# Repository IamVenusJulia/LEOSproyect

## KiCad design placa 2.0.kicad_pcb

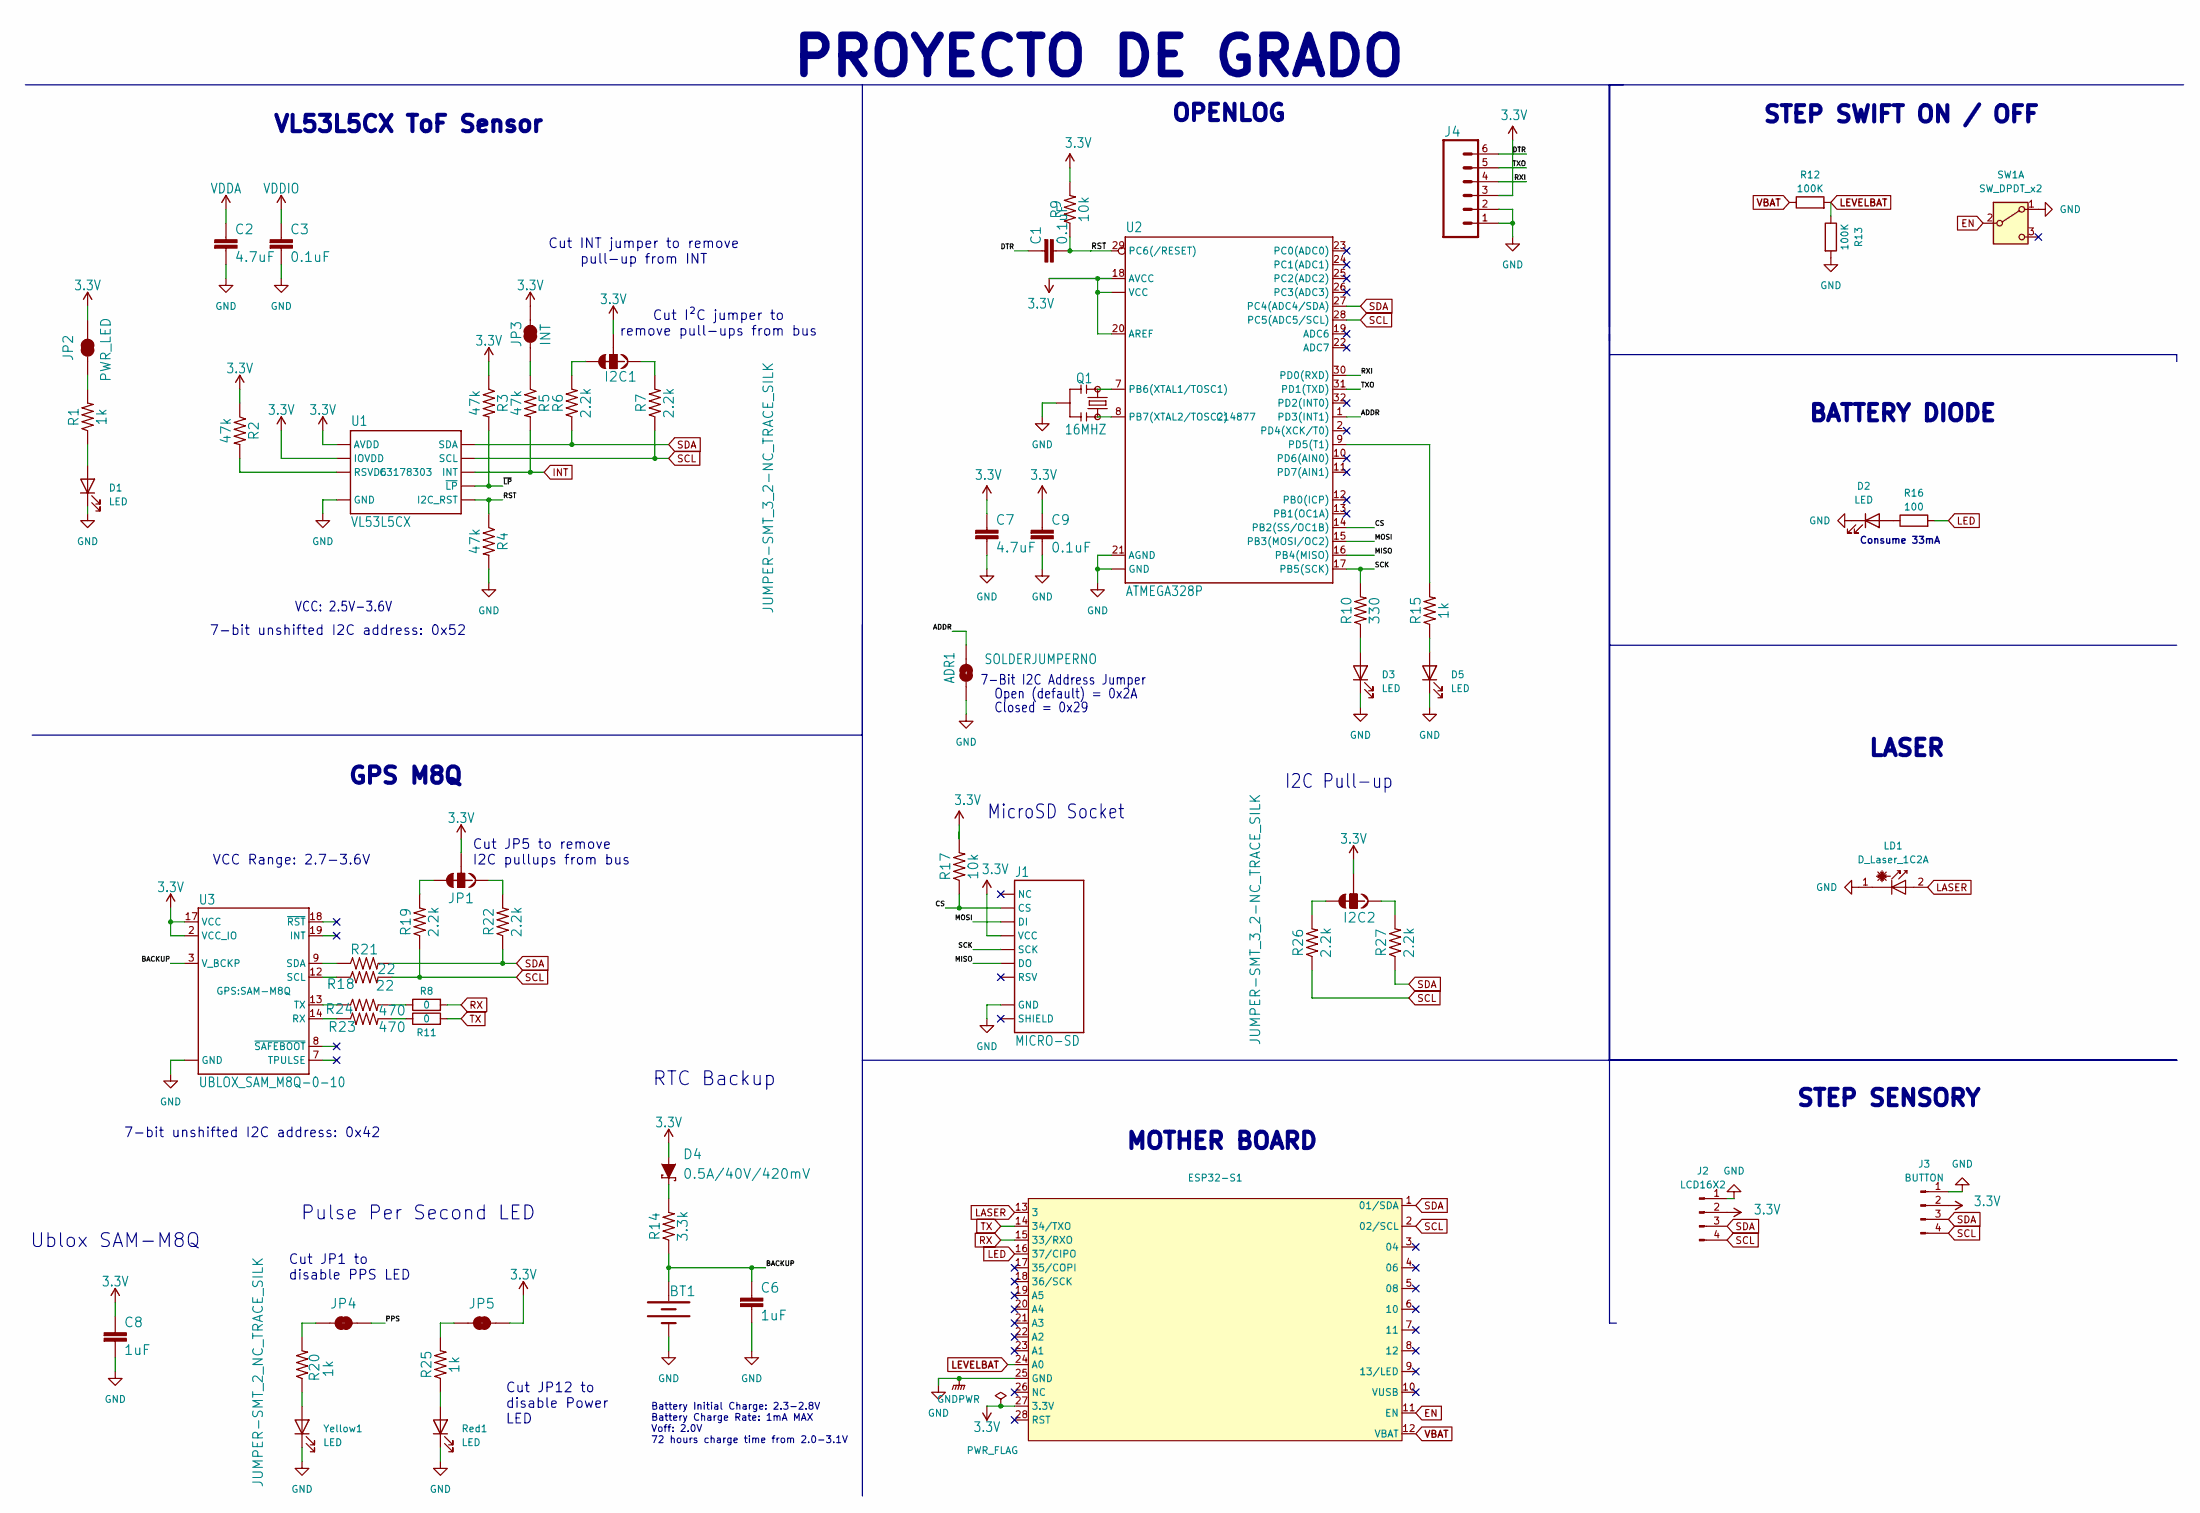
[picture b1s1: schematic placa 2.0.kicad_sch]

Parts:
ADR1: SOLDERJUMPERNO; SJ_2S-NO
BT1: 6.8MM_COIN_CELL; ML414H_IV01E
C1, C3, C9: 0.1uF; C_0603_1608Metric
C2, C7: 4.7uF; C_0603_1608Metric
C6, C8: 1uF; C_0603_1608Metric
D1, D3, D5: LED; LED_1206_3216Metric
D2: LED; LED_D3.0mm_Horizontal_O6.35mm_Z10.0mm
D4: 0.5A/40V/420mV; D_SOD-323
ESP32-S1: ESP32-S2
I2C1, I2C2: JUMPER-SMT_3_2-NC_TRACE_SILK; SMT-JUMPER_3_2-NC_TRACE_SILK
J1: MICRO-SD; MICRO-SD-SOCKET
J2: LCD16X2; JST_PH_B4B-PH-K_1x04_P2.00mm_Vertical
J3: BUTTON; JST_PH_B4B-PH-K_1x04_P2.00mm_Vertical
J4: CONN_06NO_SILK_NO_POP; PinHeader_1x06_P2.54mm_Vertical
JP1: JUMPER-SMT_3_2-NC_TRACE_SILK; SMT-JUMPER_3_2-NC_TRACE_SILK
JP2: PWR_LED; SMT-JUMPER_2_NC_TRACE_SILK
JP3: INT; SMT-JUMPER_2_NC_TRACE_SILK
JP4, JP5: JUMPER-SMT_2_NC_TRACE_SILK; SMT-JUMPER_2_NC_TRACE_SILK
LD1: D_Laser_1C2A; LaserDiode_TO18-D5.6-3
Q1: 16MHZ; RESONATOR-SMD
R1, R15, R20, R25: 1k; R_0603_1608Metric
R2, R3, R4, R5: 47k; R_0603_1608Metric
R6, R7, R19, R22, R26, R27: 2.2k; R_0603_1608Metric
R8, R11: 0; 1206
R9, R17: 10k; R_0603_1608Metric
R10: 330; R_0603_1608Metric
R12, R13: 100K; 1206
R14: 3.3k; R_0603_1608Metric
R16: 100; 1206
R18, R21: 22; R_0603_1608Metric
R23, R24: 470; R_0603_1608Metric
Red1: LED; LED_1206_3216Metric
SW1: SW_DPDT_x2; Molex_KK-254_AE-6410-02A_1x02_P2.54mm_Vertical
U1: VL53L5CX; LCSC C3178303
U2: ATMEGA328P; TQFP-32_7x7mm; LCSC C14877
U3: UBLOX_SAM_M8Q-0-10; SAM-M8Q
Yellow1: LED; LED_1206_3216Metric

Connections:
3.3V: C7.1, C8.1, C9.1, D4.2 (A), ESP32-S1.27 (3.3V), I2C1.2, I2C2.2, J1.VCC, J2.2, J3.2, J4.3, JP1.2, JP2.2, JP3.2, JP5.2, R2.1, R3.1, R9.2, R17.2, U1.A4 (IOVDD), U1.B1 (AVDD), U1.B7 (AVDD), U2.4 (VCC), U2.6 (VCC), U2.18 (AVCC), U2.20 (AREF), U3.2 (VCC_IO), U3.17 (VCC)
/ADDR: ADR1.2, U2.1 (PD3(INT1))
/BACKUP: BT1.+, C6.1, R14.1, U3.3 (V_BCKP)
/CS: J1.CS, R17.1, U2.14 (PB2(SS/OC1B))
/DTR: C1.2, J4.6
/MISO: J1.DO, U2.16 (PB4(MISO))
/MOSI: J1.DI, U2.15 (PB3(MOSI/OC2))
/PPS: JP4.2
/RST: C1.1, R4.1, R9.1, U1.A1 (I2C_RST), U2.29 (PC6(/RESET))
/RXI: J4.4, U2.30 (PD0(RXD))
/SCK: J1.SCLK (SCK), R10.2, U2.17 (PB5(SCK))
/TXO: J4.5, U2.31 (PD1(TXD))
/~LP: R3.2, U1.A5 (~LP)
EN: ESP32-S1.11 (EN), SW1.2 (B)
GND: ADR1.1, BT1.-, C2.2, C3.2, C6.2, C7.2, C8.2, C9.2, D1.1 (K), D2.1 (K), D3.1 (K), D5.1 (K), ESP32-S1.25 (GND), J1.GND, J2.1, J3.1, J4.1, J4.2, LD1.1 (K), Q1.2, R4.2, R13.2, Red1.1 (K), SW1.1 (A), U1.A2 (GND), U1.A6 (GND), U1.A7 (GND), U1.B4 (GND), U1.C1 (GND), U1.C6 (GND), U1.C7 (GND), U2.3 (GND), U2.5 (GND), U2.21 (AGND), U3.1 (GND), U3.4 (GND), U3.5 (GND), U3.6 (GND), U3.10 (GND), U3.11 (GND), U3.15 (GND), U3.16 (GND), U3.20 (GND), Yellow1.1 (K)
INT: R5.2, U1.A3 (INT)
LASER: ESP32-S1.13 (3), LD1.2 (A)
LED: ESP32-S1.16 (37/CIPO), R16.2
LEVELBAT: ESP32-S1.24 (A0), R12.2, R13.1
unnamed: D1.2 (A), R1.1
unnamed: D2.2 (A), R16.1
unnamed: D3.2 (A), R10.1
unnamed: D4.1 (C), R14.2
unnamed: D5.2 (A), R15.1
unnamed: I2C1.1, R7.2
unnamed: I2C1.3, R6.2
unnamed: I2C2.1, R27.2
unnamed: I2C2.3, R26.2
unnamed: JP1.1, R22.2
unnamed: JP1.3, R19.2
unnamed: JP2.1, R1.2
unnamed: JP3.1, R5.1
unnamed: JP4.1, R20.2
unnamed: JP5.1, R25.2
unnamed: R11.1, R23.2
unnamed: R8.1, R24.2
unnamed: R25.1, Red1.2 (A)
unnamed: R2.2, U1.C2 (RSVD6)
unnamed: Q1.3, U2.7 (PB6(XTAL1/TOSC1))
unnamed: Q1.1, U2.8 (PB7(XTAL2/TOSC2))
unnamed: R15.2, U2.9 (PD5(T1))
unnamed: R23.1, U3.14 (RX)
unnamed: R18.1, U3.12 (SCL)
unnamed: R21.1, U3.9 (SDA)
unnamed: R24.1, U3.13 (TX)
unnamed: R20.1, Yellow1.2 (A)
RX: ESP32-S1.15 (33/RXO), R8.2
SCL: ESP32-S1.2 (02/SCL), J2.4, J3.4, R7.1, R18.2, R19.1, R26.1, U1.C4 (SCL), U2.28 (PC5(ADC5/SCL))
SDA: ESP32-S1.1 (01/SDA), J2.3, J3.3, R6.1, R21.2, R22.1, R27.1, U1.C3 (SDA), U2.27 (PC4(ADC4/SDA))
TX: ESP32-S1.14 (34/TXO), R11.2
VBAT: ESP32-S1.12 (VBAT), R12.1
VDDA: C2.1
VDDIO: C3.1

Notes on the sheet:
Cut JP12 to disable Power LED
Cut JP5 to remove I2C pullups from bus
VCC Range: 2.7-3.6V
Pulse Per Second LED
PROYECTO DE GRADO
BATTERY DIODE
Consume 33mA
Cut I²C jumper to remove pull-ups from bus
Cut INT jumper to remove pull-up from INT
RTC Backup
VCC: 2.5V-3.6V
GPS M8Q
7-Bit I2C Address Jumper
Cut JP1 to disable PPS LED
Ublox SAM-M8Q
7-bit unshifted I2C address: 0x52
STEP SWIFT ON / OFF
MOTHER BOARD
Closed = 0x29
STEP SENSORY
VL53L5CX ToF Sensor
I2C Pull-up
OPENLOG
LASER
Open (default) = 0x2A
MicroSD Socket
Battery Initial Charge: 2.3-2.8V Battery Charge Rate: 1mA MAX Voff: 2.0V 72 hours charge time from 2.0-3.1V
7-bit unshifted I2C address: 0x42

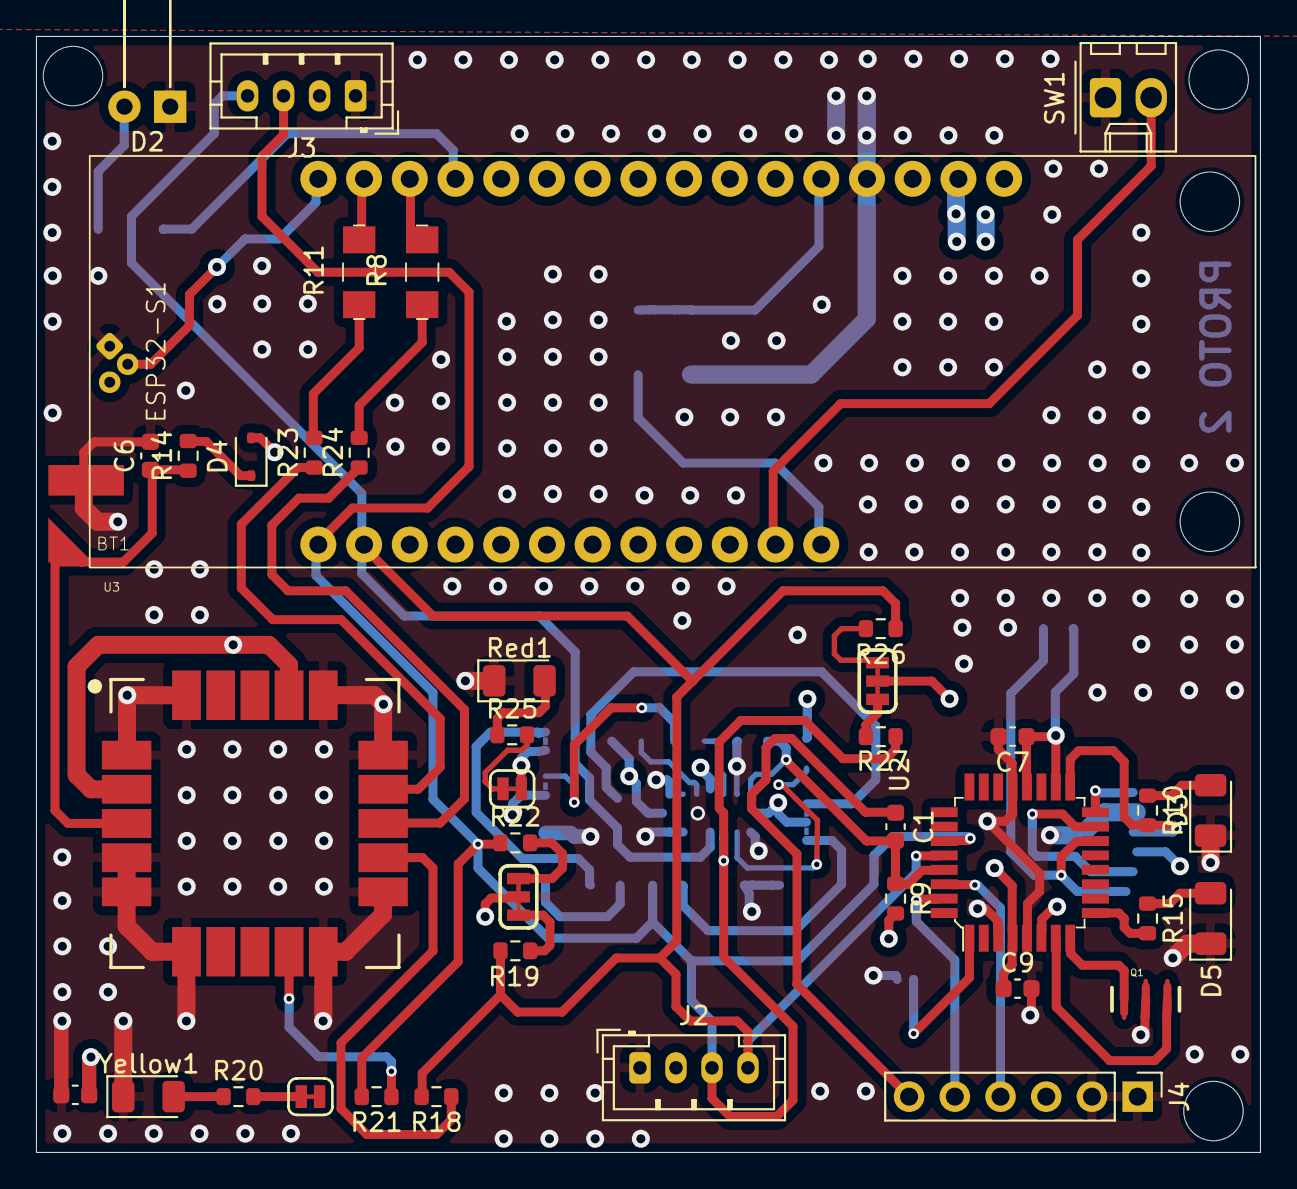
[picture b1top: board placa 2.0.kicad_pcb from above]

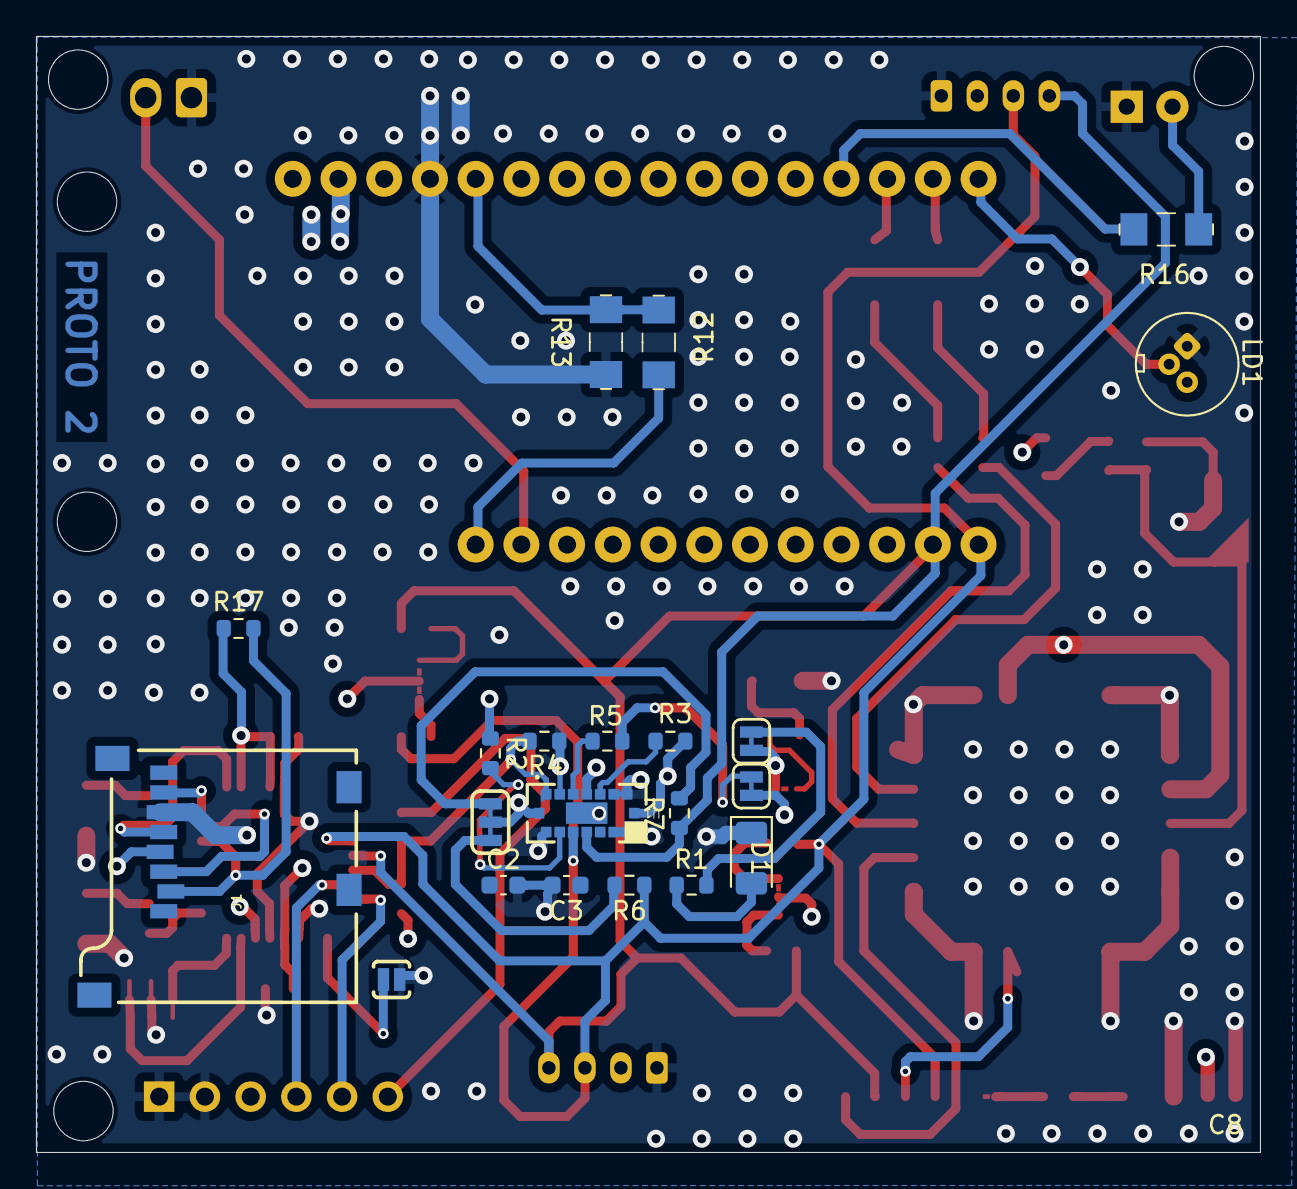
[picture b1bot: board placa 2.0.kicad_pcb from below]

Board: 4 copper layers, 68.0 x 62.0 mm, 61 parts (21 on the bottom side), 50 nets.

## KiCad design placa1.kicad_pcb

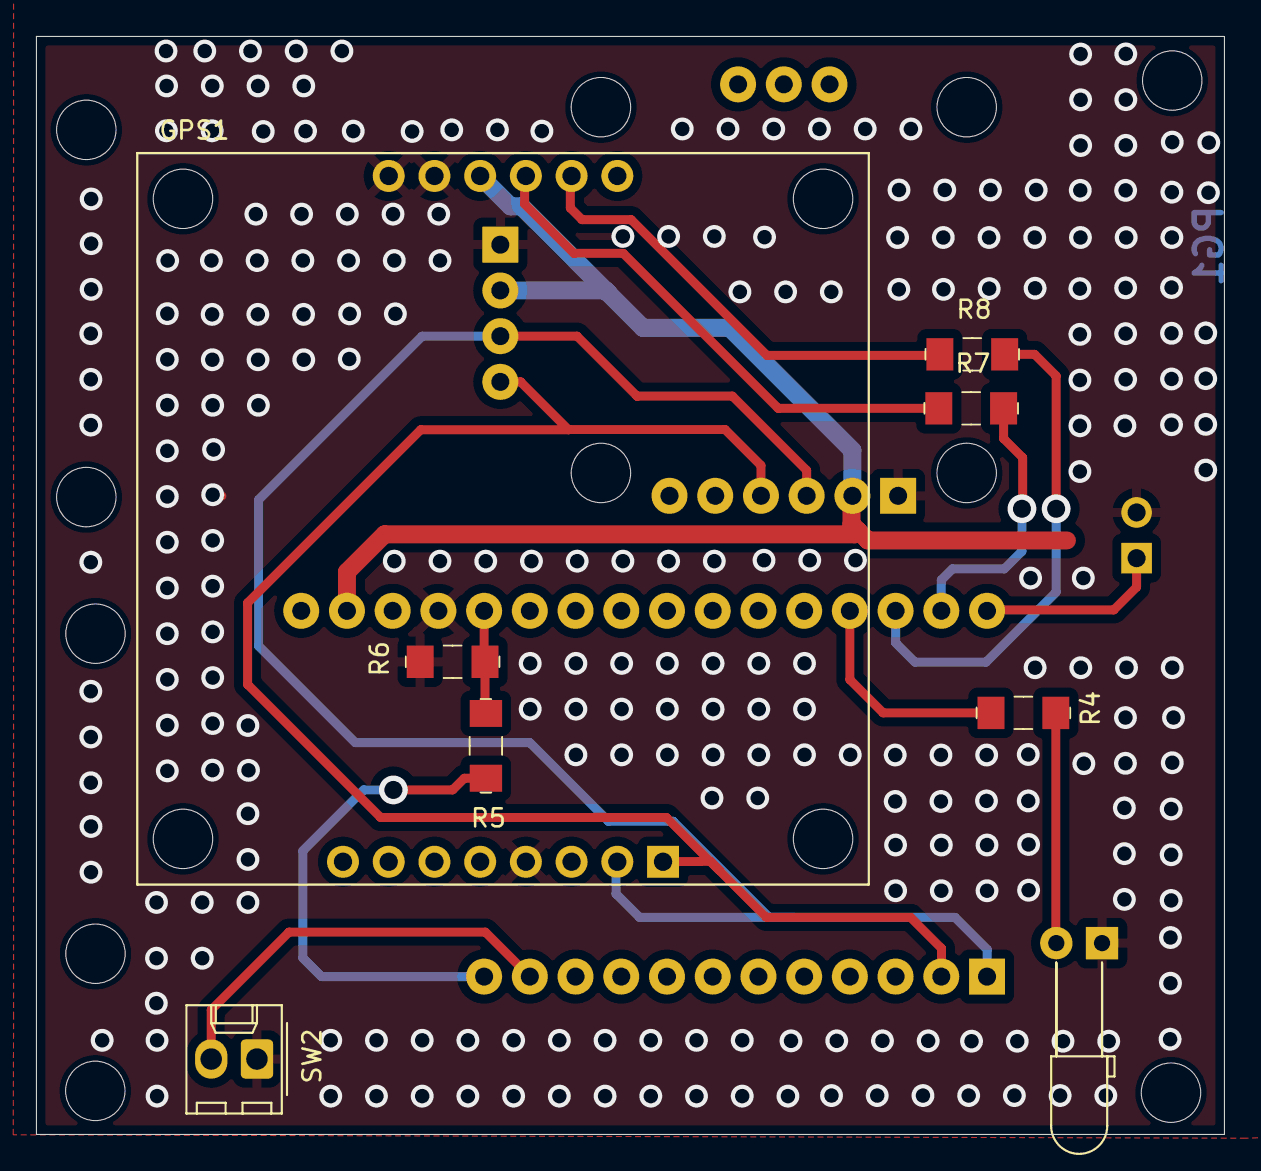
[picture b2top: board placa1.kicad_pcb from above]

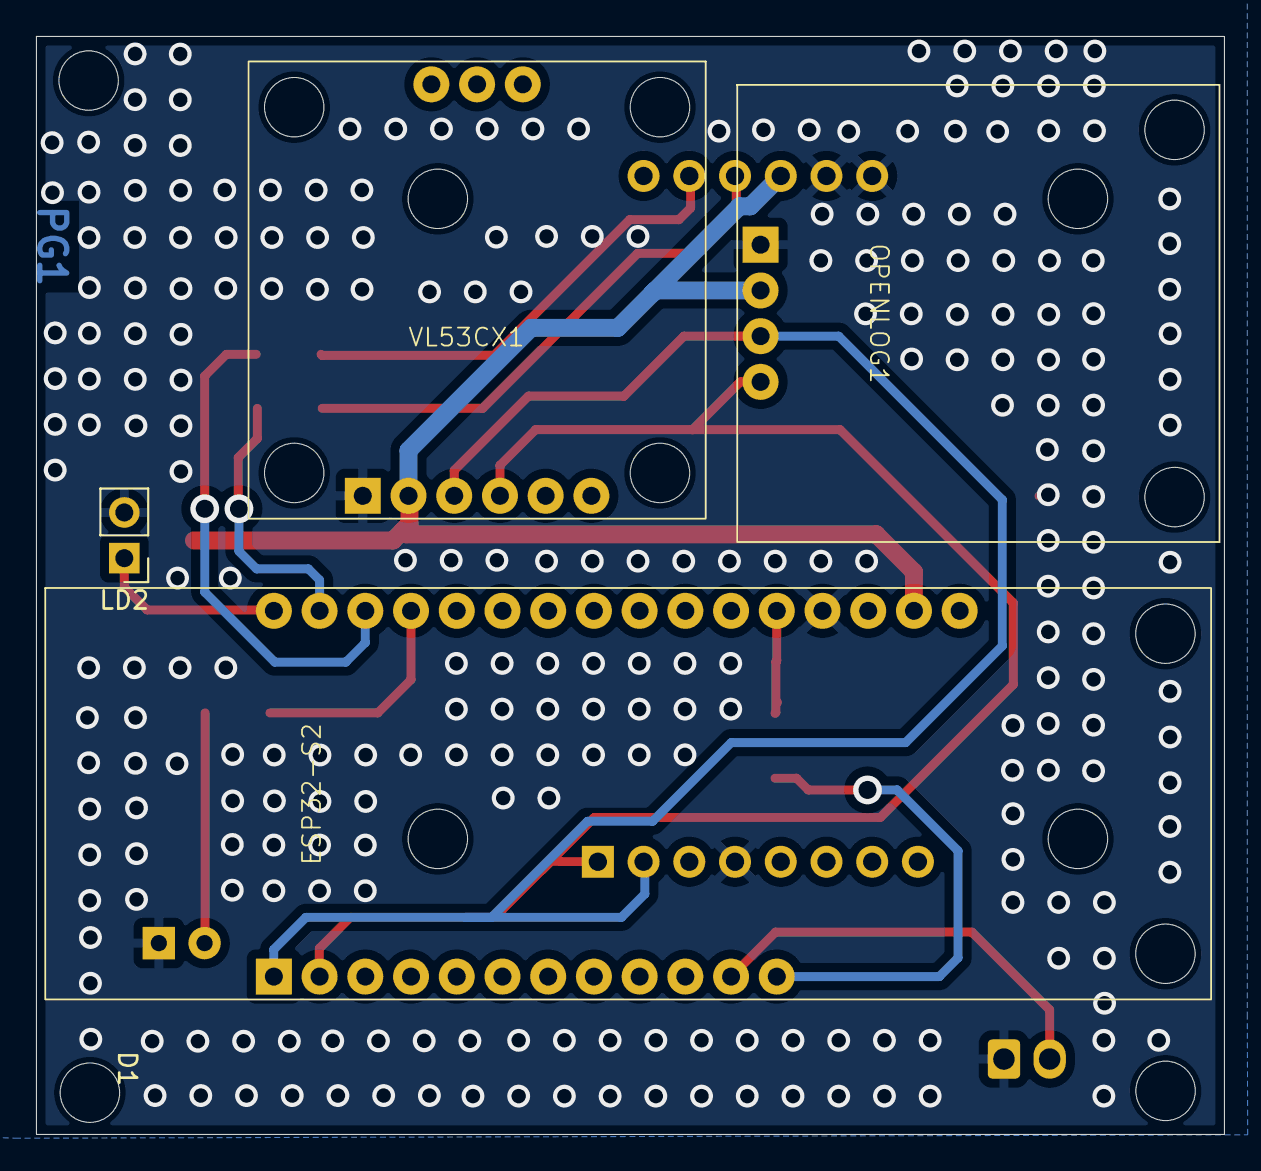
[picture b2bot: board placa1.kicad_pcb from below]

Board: 2 copper layers, 66.0 x 61.0 mm, 12 parts (3 on the bottom side), 14 nets.

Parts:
D1: LED; LED_D3.0mm_Horizontal_O6.35mm_Z10.0mm
ESP32-S2: ESP32-S2
GPS1: GPS-15210; MODULE_GPS-15210
LD2: D_Laser_1C2A; PinHeader_1x02_P2.54mm_Vertical
OPENLOG1: OPENLOG
R4: 100; 1206
R5, R6: 100K; 1206
R7, R8: 0; 1206
SW2: SW_DPDT_x2; Molex_KK-254_AE-6410-02A_1x02_P2.54mm_Vertical
VL53CX1: VL53CX

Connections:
+3.3V: ESP32-S2.27 (3.3V), GPS1.J3_3 (3.3V), GPS1.J4_3 (3.3V), OPENLOG1.3 (SDA), VL53CX1.2 (3.3V)
EN: ESP32-S2.11 (EN), SW2.2 (B)
GND: D1.1 (K), ESP32-S2.25 (GND), GPS1.J3_4 (GND), GPS1.J4_1 (GND), GPS1.J4_2 (GND), LD2.2 (A), OPENLOG1.4 (SCL), R6.2, SW2.1 (A), VL53CX1.1 (GND)
LASER: ESP32-S2.13 (3), LD2.1 (K)
LED: ESP32-S2.16 (37/CIPO), R4.2
LEVELBAT: ESP32-S2.24 (A0), R5.2, R6.1
unnamed: D1.2 (A), R4.1
unnamed: GPS1.J4_4 (RXI), R7.1
unnamed: GPS1.J4_5 (TXO), R8.1
RX: ESP32-S2.14 (34/TXO), R7.2
SCL: ESP32-S2.2 (02/SCL), GPS1.J3_1 (SCL), OPENLOG1.1 (GND), VL53CX1.4 (SCL)
SDA: ESP32-S2.1 (01/SDA), GPS1.J3_2 (SDA), OPENLOG1.2 (3.3V), VL53CX1.3 (SDA)
TX: ESP32-S2.15 (33/RXO), R8.2
VBAT: ESP32-S2.12 (VBAT), R5.1

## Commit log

2024-11-23 archivos
